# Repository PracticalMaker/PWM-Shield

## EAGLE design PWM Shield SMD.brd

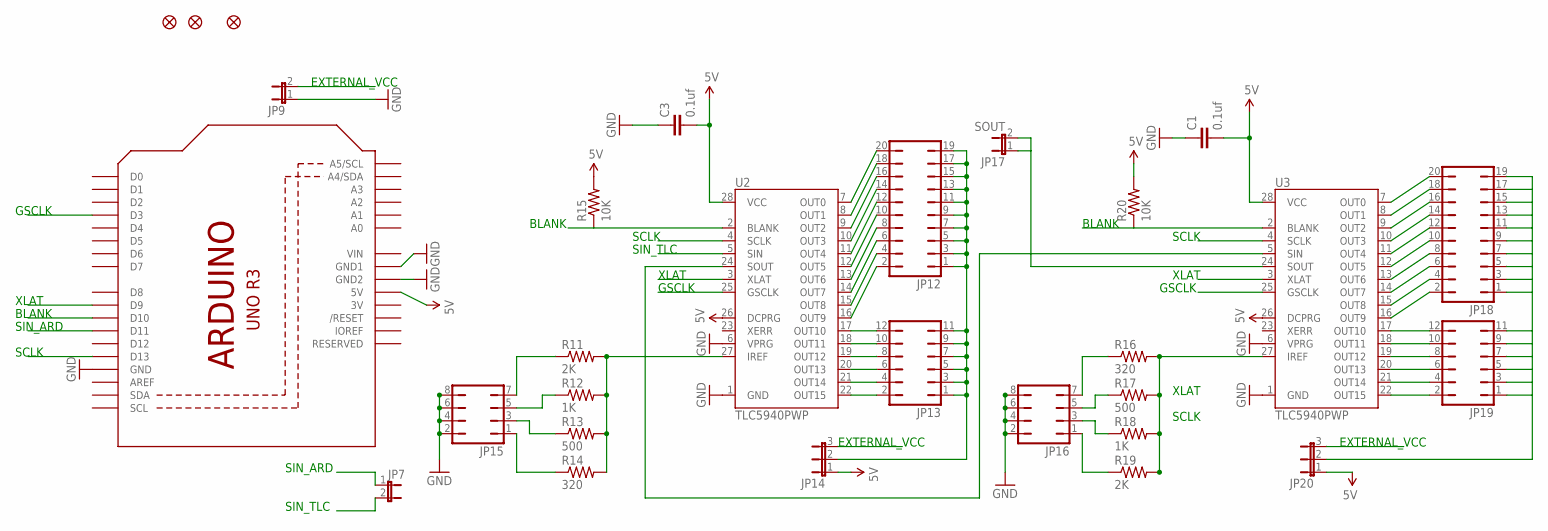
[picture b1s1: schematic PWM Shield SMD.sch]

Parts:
C1, C3: 0.1uf; C0603
JP1, JP2, JP3: FIDUCIAL1.5X3; FIDUCIAL-1.5X3
JP7, JP9: JP1E; JP1
JP12, JP18: JP10Q
JP13, JP19: JP6Q
JP14, JP20: JP2E; JP2
JP15, JP16: JP4Q
JP17: SOUT; JP1
R11, R19: 2K; R0603
R12, R18: 1K; 0204/7
R13, R17: 500; 0204/7
R14, R16: 320; 0204/7
R15, R20: 10K; R0603
U1: ARDUINOR3-DIMENSION; ARDUINOR3
U2, U3: TLC5940PWP; TSSOP28-GROUNDPAD

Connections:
3V: U1.3V
5V: C1.2, C3.2, JP14.1, JP20.1, R15.2, R20.2, U1.5V, U2.26 (DCPRG), U2.28 (VCC), U3.26 (DCPRG), U3.28 (VCC)
BLANK: R15.1, R20.1, U1.D10, U2.2 (BLANK), U3.2 (BLANK)
EXTERNAL_VCC: JP9.2, JP14.3, JP20.3
GND: C1.1, C3.1, JP9.1, JP15.2, JP15.4, JP15.6, JP15.8, JP16.2, JP16.4, JP16.6, JP16.8, U1.GND, U1.GND1, U1.GND2, U2.1 (GND), U2.6 (VPRG), U3.1 (GND), U3.6 (VPRG)
GSCLK: U1.D3, U2.25 (GSCLK), U3.25 (GSCLK)
unnamed: JP17.1, JP17.2, U3.24 (SOUT)
unnamed: JP12.2, U2.16 (OUT9)
unnamed: JP12.4, U2.15 (OUT8)
unnamed: JP12.6, U2.14 (OUT7)
unnamed: JP12.8, U2.13 (OUT6)
unnamed: JP12.10, U2.12 (OUT5)
unnamed: JP12.12, U2.11 (OUT4)
unnamed: JP12.14, U2.10 (OUT3)
unnamed: JP12.16, U2.9 (OUT2)
unnamed: JP12.18, U2.8 (OUT1)
unnamed: JP12.20, U2.7 (OUT0)
unnamed: JP13.2, U2.22 (OUT15)
unnamed: JP13.4, U2.21 (OUT14)
unnamed: JP13.6, U2.20 (OUT13)
unnamed: JP13.8, U2.19 (OUT12)
unnamed: JP13.10, U2.18 (OUT11)
unnamed: JP13.12, U2.17 (OUT10)
unnamed: JP12.1, JP12.3, JP12.5, JP12.7, JP12.9, JP12.11, JP12.13, JP12.15, JP12.17, JP12.19, JP13.1, JP13.3, JP13.5, JP13.7, JP13.9, JP13.11, JP14.2
unnamed: R11.2, R12.2, R13.2, R14.2, U2.27 (IREF)
unnamed: JP15.1, R14.1
unnamed: JP15.3, R13.1
unnamed: JP15.5, R12.1
unnamed: JP15.7, R11.1
unnamed: R16.2, R17.2, R18.2, R19.2, U3.27 (IREF)
unnamed: JP16.1, R19.1
unnamed: JP16.3, R18.1
unnamed: JP16.5, R17.1
unnamed: JP16.7, R16.1
unnamed: JP18.2, U3.16 (OUT9)
unnamed: JP18.4, U3.15 (OUT8)
unnamed: JP18.6, U3.14 (OUT7)
unnamed: JP18.8, U3.13 (OUT6)
unnamed: JP18.10, U3.12 (OUT5)
unnamed: JP18.12, U3.11 (OUT4)
unnamed: JP18.14, U3.10 (OUT3)
unnamed: JP18.16, U3.9 (OUT2)
unnamed: JP18.18, U3.8 (OUT1)
unnamed: JP18.20, U3.7 (OUT0)
unnamed: JP19.2, U3.22 (OUT15)
unnamed: JP19.4, U3.21 (OUT14)
unnamed: JP19.6, U3.20 (OUT13)
unnamed: JP19.8, U3.19 (OUT12)
unnamed: JP19.10, U3.18 (OUT11)
unnamed: JP19.12, U3.17 (OUT10)
unnamed: JP18.1, JP18.3, JP18.5, JP18.7, JP18.9, JP18.11, JP18.13, JP18.15, JP18.17, JP18.19, JP19.1, JP19.3, JP19.5, JP19.7, JP19.9, JP19.11, JP20.2
SCLK: U1.D13, U2.4 (SCLK), U3.4 (SCLK)
SIN_ARD: JP7.1, U1.D11
SIN_TLC: JP7.2, U2.5 (SIN)
SOUT_1: U2.24 (SOUT), U3.5 (SIN)
VIN: U1.VIN
XLAT: U1.D9, U2.3 (XLAT), U3.3 (XLAT)

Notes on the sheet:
SIN_ARD
SIN_TLC
EXTERNAL_VCC
BLANK
GSCLK
XLAT
SCLK

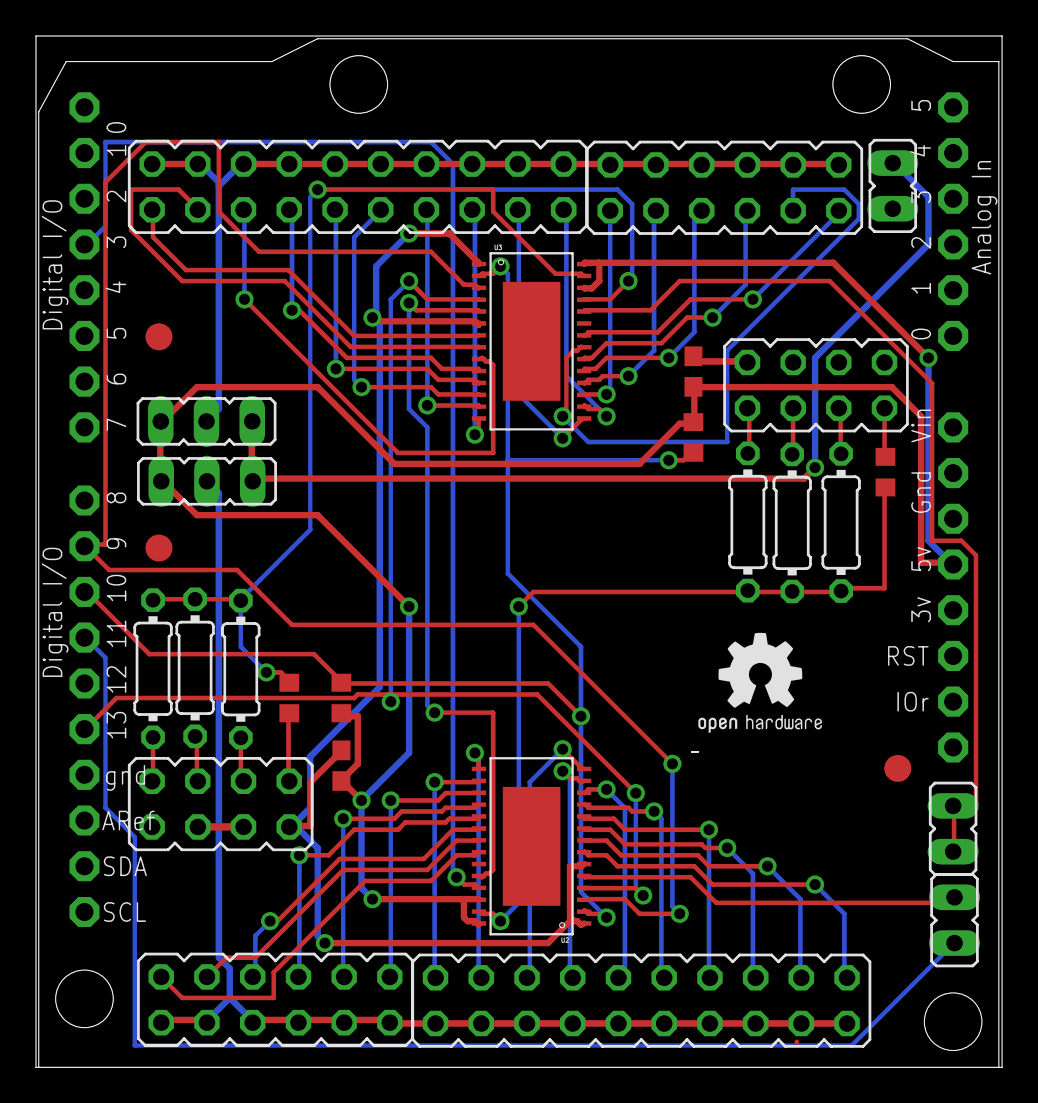
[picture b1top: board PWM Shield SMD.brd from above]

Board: 2 copper layers, 53.7 x 57.3 mm, 30 parts (0 on the bottom side), 55 nets.

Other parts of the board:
U$2: OSHW2

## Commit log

2014-09-03 remove ds store
